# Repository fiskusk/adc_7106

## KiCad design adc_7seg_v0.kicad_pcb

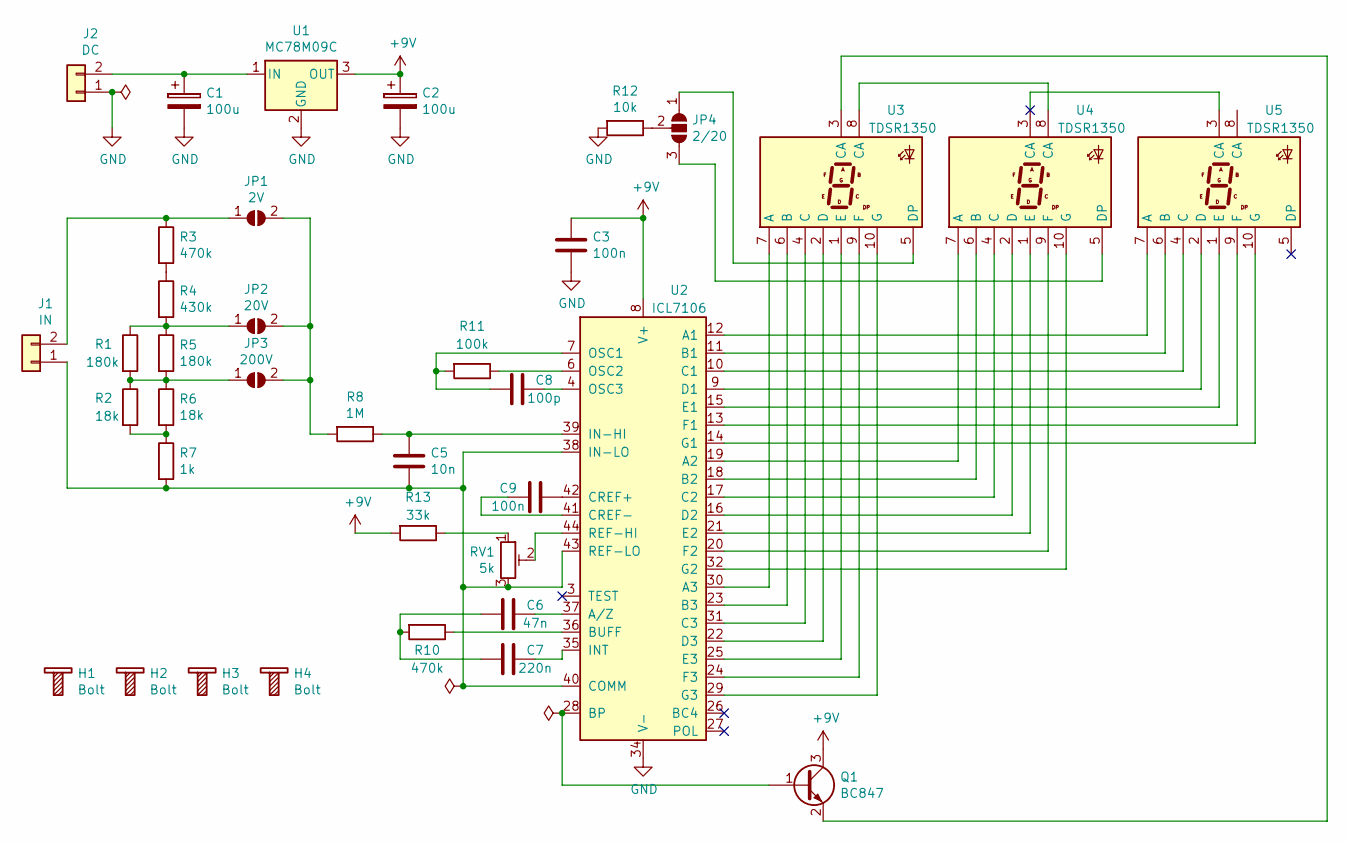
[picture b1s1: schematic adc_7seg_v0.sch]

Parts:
C1, C2: 100u; CP_Radial_D8.0mm_P3.50mm
C3, C9: 100n; C_0603_1608Metric
C5: 10n; C_0603_1608Metric
C6: 47n; C_0603_1608Metric
C7: 220n; C_0603_1608Metric
C8: 100p; C_0603_1608Metric
H1, H2, H3, H4: Bolt; Bolt_M3
J1: IN; Molex_KK-254_AE-6410-02A_1x02_P2.54mm_Vertical
J2: DC; Molex_KK-254_AE-6410-02A_1x02_P2.54mm_Vertical
JP1: 2V; Jumper
JP2: 20V; Jumper
JP3: 200V; Jumper
JP4: 2/20; SolderJumper-3_P1.3mm_Open_Pad1.0x1.5mm_NumberLabels
Q1: BC847; SOT-23
R1, R5: 180k; R_0603_1608Metric
R2, R6: 18k; R_0603_1608Metric
R3, R10: 470k; R_0603_1608Metric
R4: 430k; R_0603_1608Metric
R7: 1k; R_0603_1608Metric
R8: 1M; R_0603_1608Metric
R11: 100k; R_0603_1608Metric
R12: 10k; R_0603_1608Metric
R13: 33k; R_0603_1608Metric
RV1: 5k; Potentiometer_SRPASSIVES_1801
U1: MC78M09C; TO-252-2
U2: ICL7106; TQFP-44_10x10mm_P0.8mm
U3, U4, U5: TDSR1350; TDSR1350_small_pads

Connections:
+9V: C2.1, C3.1, Q1.3 (C), R13.2, U1.3 (OUT), U2.8 (V+)
GND: C1.2, C2.2, C3.2, J2.1, R12.2, U1.2 (GND), U2.34 (V-)
unnamed: C1.1, J2.2, U1.1 (IN)
unnamed: C5.1, R8.1, U2.39 (IN-HI)
unnamed: C5.2, J1.1, R7.2, RV1.3, U2.38 (IN-LO), U2.40 (COMM), U2.43 (REF-LO)
unnamed: C6.1, U2.37 (A/Z)
unnamed: C6.2, C7.2, R10.2
unnamed: C7.1, U2.35 (INT)
unnamed: C8.1, U2.4 (OSC3)
unnamed: C8.2, R11.2, U2.7 (OSC1)
unnamed: C9.1, U2.42 (CREF+)
unnamed: C9.2, U2.41 (CREF-)
unnamed: J1.2, JP1.1 (A), R3.1
unnamed: JP1.2 (B), JP2.2 (B), JP3.2 (B), R8.2
unnamed: JP2.1 (A), R1.1, R4.2, R5.1
unnamed: JP3.1 (A), R1.2, R2.1, R5.2, R6.1
unnamed: JP4.1 (A), U3.5 (DP)
unnamed: JP4.2 (C), R12.1
unnamed: JP4.3 (B), U4.5 (DP)
unnamed: Q1.1 (B), U2.28 (BP)
unnamed: Q1.2 (E), U3.3 (CA)
unnamed: R2.2, R6.2, R7.1
unnamed: R3.2, R4.1
unnamed: R10.1, U2.36 (BUFF)
unnamed: R11.1, U2.6 (OSC2)
unnamed: R13.1, RV1.1
unnamed: RV1.2, U2.44 (REF-HI)
unnamed: U2.9 (D1), U5.2 (D)
unnamed: U2.10 (C1), U5.4 (C)
unnamed: U2.11 (B1), U5.6 (B)
unnamed: U2.12 (A1), U5.7 (A)
unnamed: U2.13 (F1), U5.9 (F)
unnamed: U2.14 (G1), U5.10 (G)
unnamed: U2.15 (E1), U5.1 (E)
unnamed: U2.16 (D2), U4.2 (D)
unnamed: U2.17 (C2), U4.4 (C)
unnamed: U2.18 (B2), U4.6 (B)
unnamed: U2.19 (A2), U4.7 (A)
unnamed: U2.20 (F2), U4.9 (F)
unnamed: U2.21 (E2), U4.1 (E)
unnamed: U2.22 (D3), U3.2 (D)
unnamed: U2.23 (B3), U3.6 (B)
unnamed: U2.24 (F3), U3.9 (F)
unnamed: U2.25 (E3), U3.1 (E)
unnamed: U2.29 (G3), U3.10 (G)
unnamed: U2.30 (A3), U3.7 (A)
unnamed: U2.31 (C3), U3.4 (C)
unnamed: U2.32 (G2), U4.10 (G)
unnamed: U3.8 (CA), U4.8 (CA)
unnamed: U4.3 (CA), U5.3 (CA)

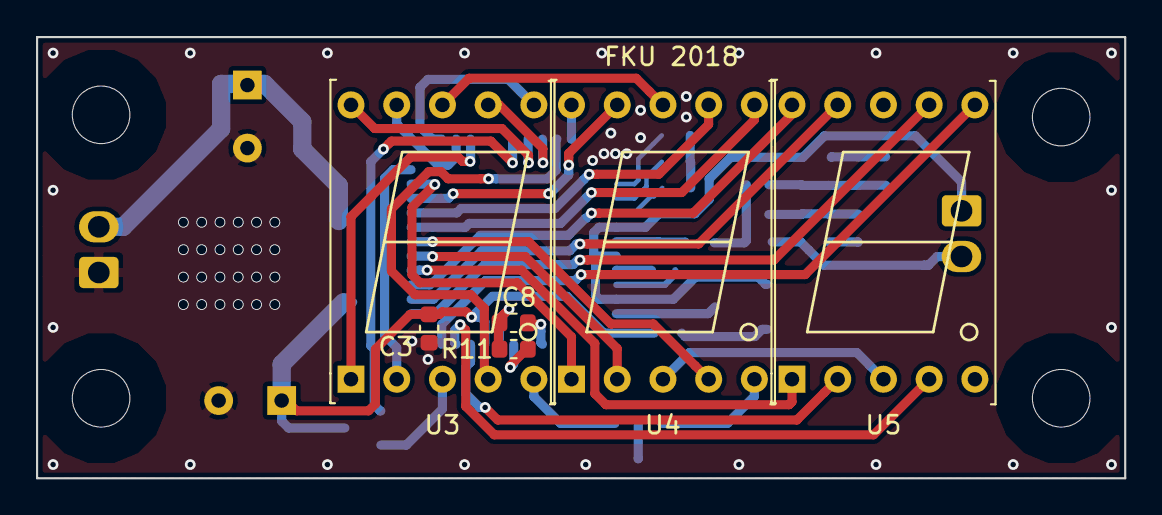
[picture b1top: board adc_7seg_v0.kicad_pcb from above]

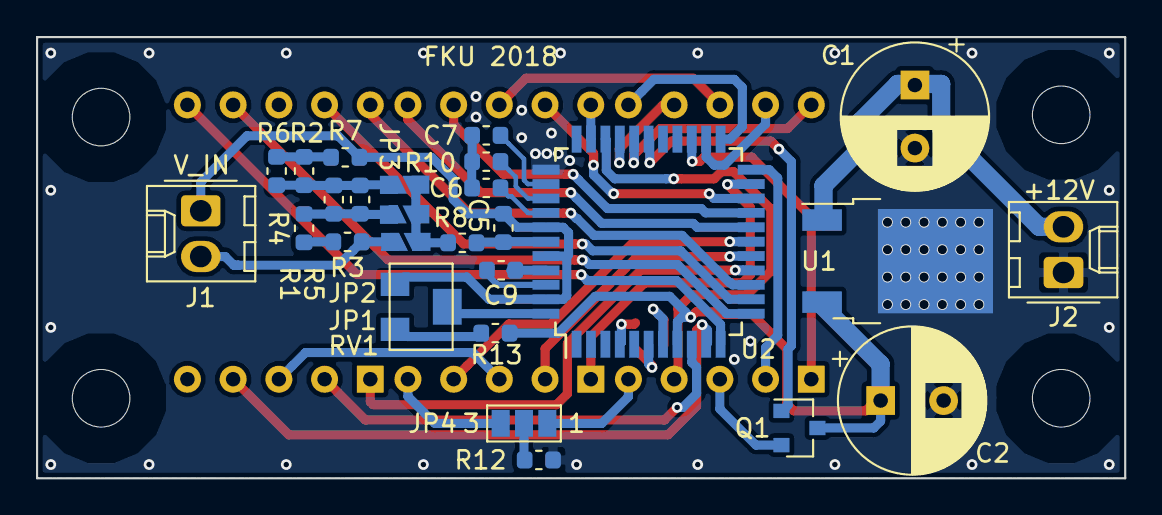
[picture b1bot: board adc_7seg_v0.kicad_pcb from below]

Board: 2 copper layers, 60.5 x 24.5 mm, 37 parts (27 on the bottom side), 50 nets.

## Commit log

2018-09-23 Added gitignore, position 7106 with pin one at left down corner
2018-09-23 Deployed the remaining parts RC
2018-09-23 last good version, skoro naroutovana
2018-09-24 last version, too big
2018-09-24 Revert "Deployed the remaining parts RC"
    This reverts commit 7c6476d39b73f4d8eff57732889eea5eef9e1166.
2018-09-24 first pokus backup
2018-09-24 update gitignore
2018-09-24 updated gitgnore, some changes, wip
2018-09-24 first pokus most of via
2018-09-24 first back up
2018-09-24 second pokus of via, update gitignore
2018-09-24 updategitignore
2018-09-25 last wip back up
2018-09-25 last wip
2018-09-25 almost last version
2018-10-02 almost last version 0.2.2
2018-10-25 last
2018-10-25 materials for production
